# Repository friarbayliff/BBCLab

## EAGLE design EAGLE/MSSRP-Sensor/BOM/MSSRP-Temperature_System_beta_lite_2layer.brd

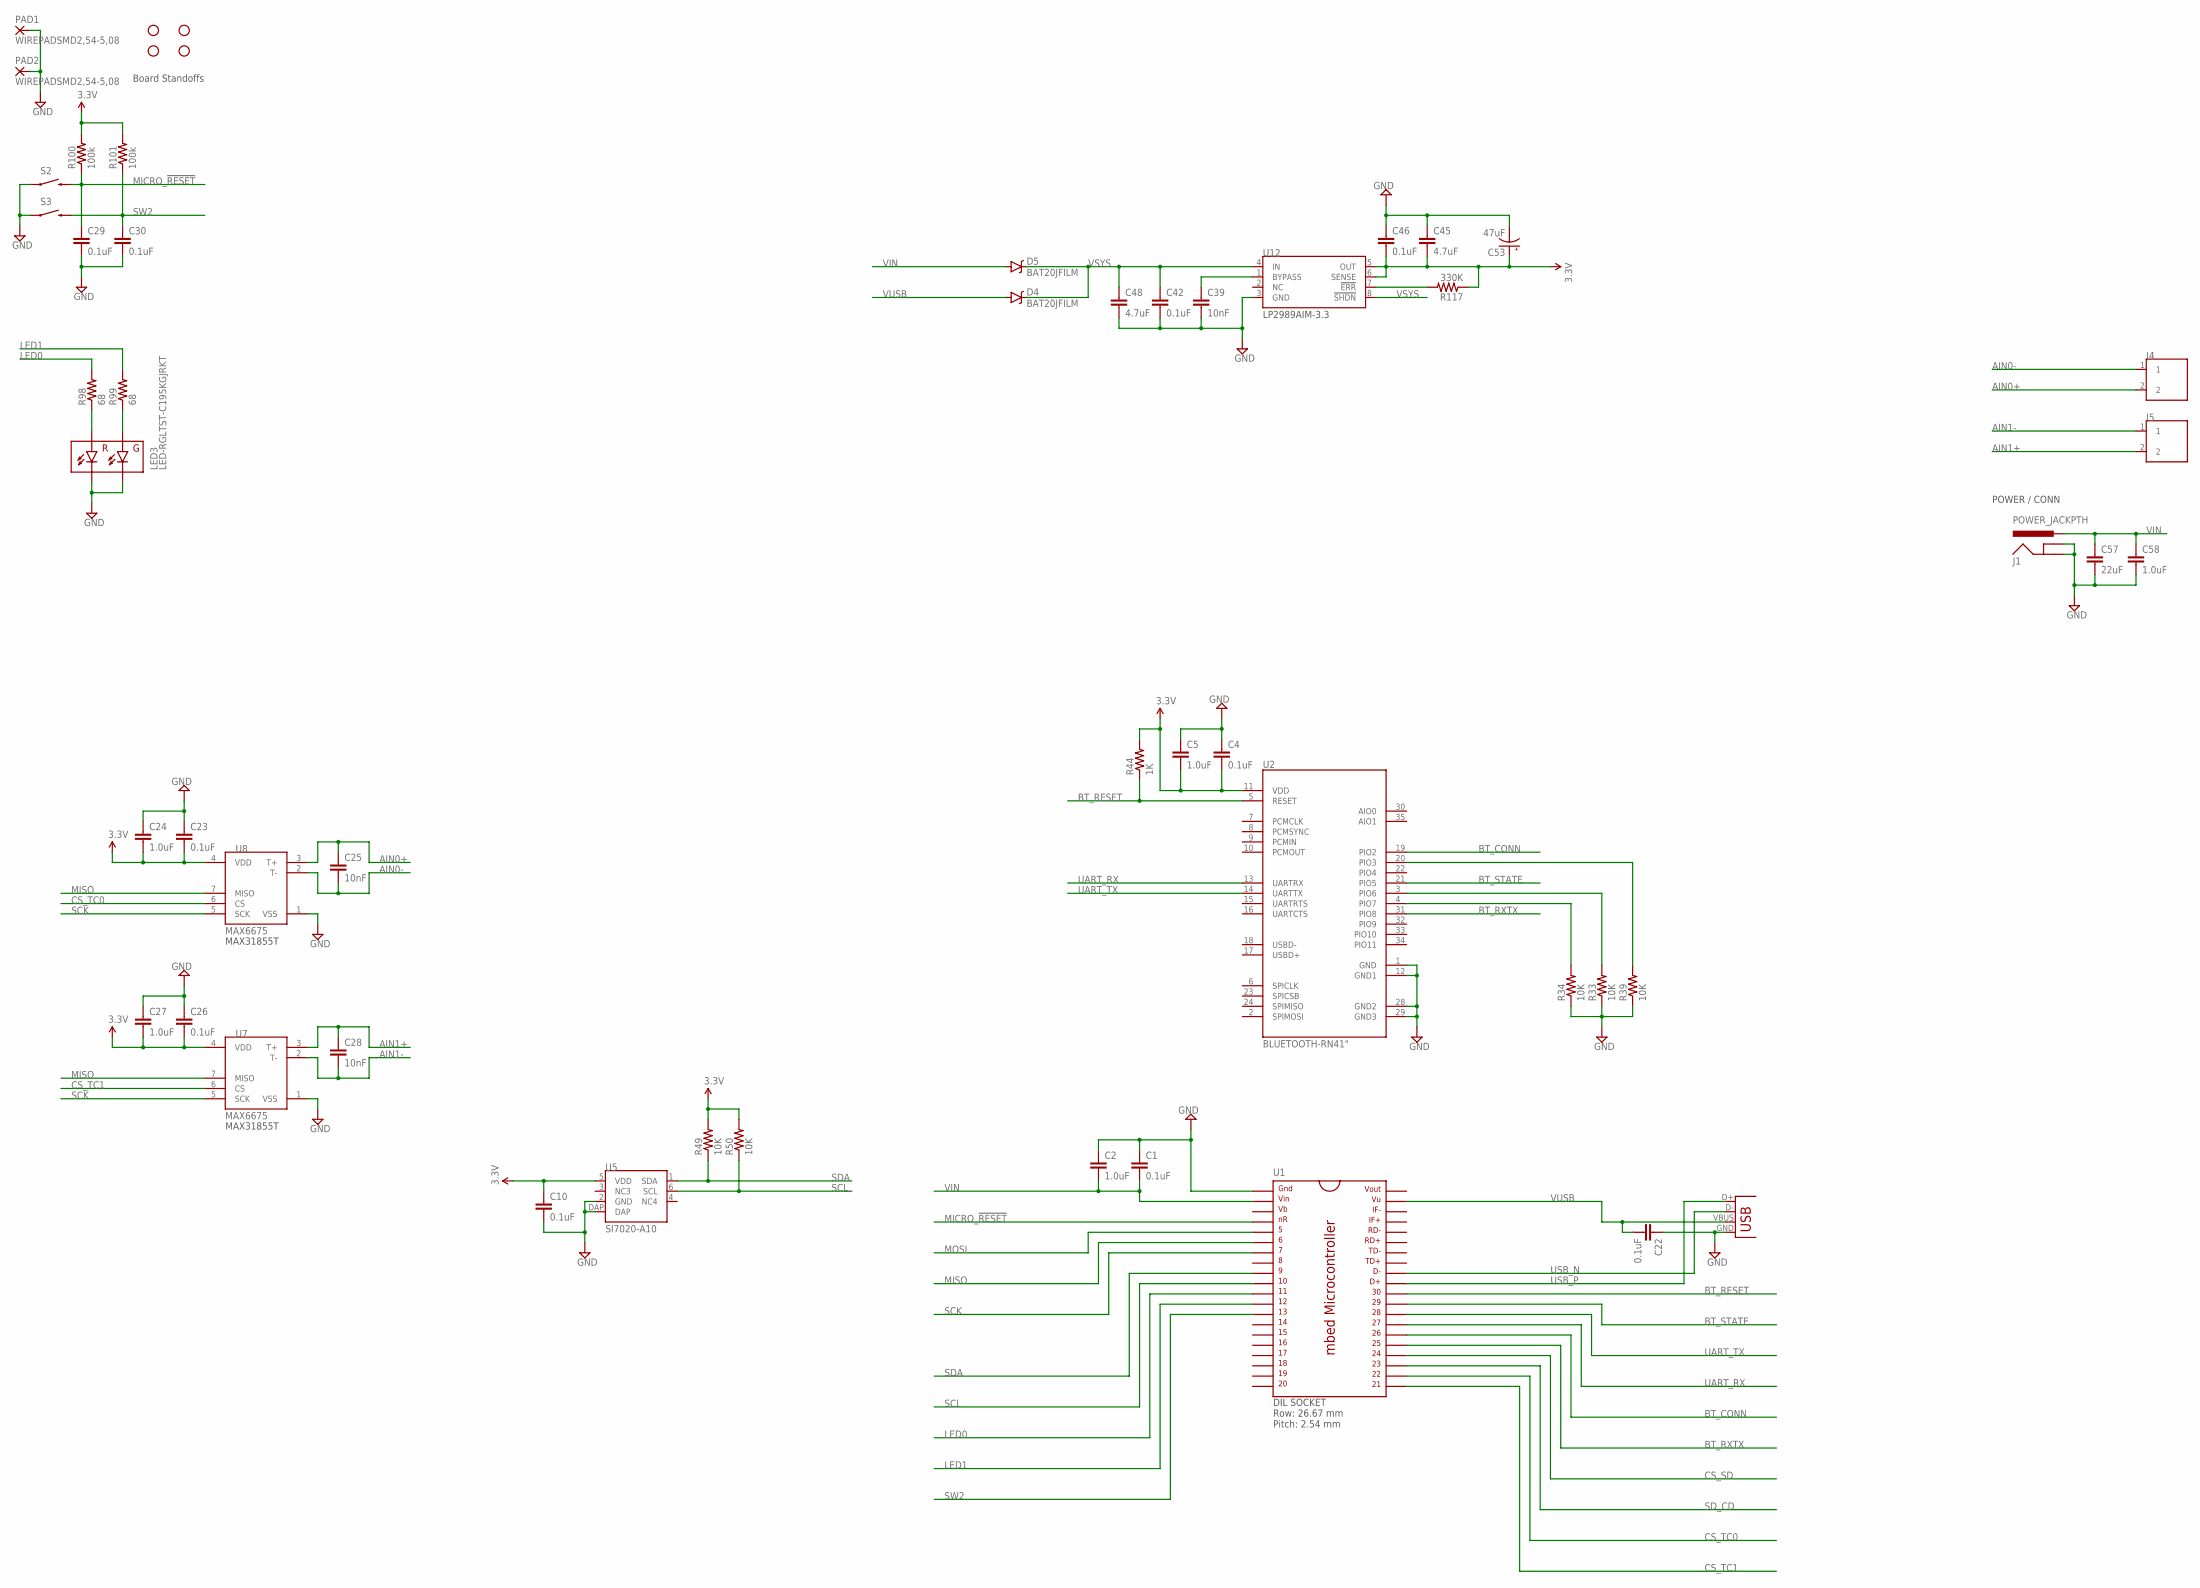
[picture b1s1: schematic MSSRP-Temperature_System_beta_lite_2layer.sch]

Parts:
C1, C4, C10, C22, C23, C26, C29, C30, C42, C46: 0.1uF; 0603-CAP
C2, C5, C24, C27, C58: 1.0uF; 0603-CAP
C25, C28, C39: 10nF; 0603-CAP
C45, C48: 4.7uF; 0603-CAP
C53: 47uF; EIA3528
C57: 22uF; 1210
D4, D5: BAT20JFILM; SOD-323
J1: POWER_JACKPTH; POWER_JACK_PTH
J4, J5: TE-2-TERMBLOCK
JP1: USB-A-SMD; USB-A-S-NOSILK-FEMALE
LED3: LED-RGLTST-C195KGJRKT; LTST-C195KGJRKT
PAD1, PAD2: WIREPADSMD2,54-5,08; SMD2,54-5,08
R33, R34, R39, R49, R50: 10K; 0603-RES
R44: 1K; 0603-RES
R98, R99: 68; 0603-RES
R100, R101: 100k; 0603-RES
R117: 330K; 0603-RES
S2, S3: SWITCH-MOMENTARY-2-SMD-1101NE; TACTILE-SWITCH-1101NE
STANDOFF1, STANDOFF2, STANDOFF3, STANDOFF4: STAND-OFF
U1: MBED; DIL40_0.9
U2: BLUETOOTH-RN41"; RN41
U5: SI7020-A10; DFN6
U7, U8: MAX6675; SO08-MAX6675
U12: LP2989AIM; SOIC8

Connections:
3.3V: C4.2, C5.2, C10.1, C23.2, C24.2, C26.2, C27.2, C45.2, C46.2, C53.A (+), R44.2, R49.2, R50.2, R100.2, R101.2, R117.1, U2.11 (VDD), U5.5 (VDD), U7.4 (VDD), U8.4 (VDD), U12.5 (OUT), U12.6 (SENSE)
AIN0+: C25.1, J4.2, U8.3 (T+)
AIN0-: C25.2, J4.1, U8.2 (T-)
AIN1+: C28.1, J5.2, U7.3 (T+)
AIN1-: C28.2, J5.1, U7.2 (T-)
BT_CONN: U1.26, U2.19 (PIO2)
BT_RESET: R44.1, U1.30, U2.5 (RESET)
BT_RXTX: U1.25, U2.31 (PIO8)
BT_STATE: U1.29, U2.21 (PIO5)
CS_SD: U1.24
CS_TC0: U1.22, U8.6 (CS)
CS_TC1: U1.21, U7.6 (CS)
GND: C1.1, C2.1, C4.1, C5.1, C10.2, C22.1, C23.1, C24.1, C26.1, C27.1, C29.2, C30.2, C39.2, C42.2, C45.1, C46.1, C48.2, C53.C (-), C57.2, C58.2, J1.GND, J1.GNDBREAK, JP1.GND, LED3.P$3 (GC), LED3.P$4 (RC), PAD1.1, PAD2.1, R33.1, R34.1, R39.1, S2.P$1 (1), S3.P$1 (1), U1.1, U2.1 (GND), U2.12 (GND1), U2.28 (GND2), U2.29 (GND3), U5.2 (GND), U5.DAP, U7.1 (VSS), U8.1 (VSS), U12.3 (GND)
LED0: R98.2, U1.11
LED1: R99.2, U1.12
MICRO_!RESET: C29.1, R100.1, S2.P$2 (2), U1.4
MISO: U1.6, U7.7 (MISO), U8.7 (MISO)
MOSI: U1.5
unnamed: R34.2, U2.4 (PIO7)
unnamed: R33.2, U2.3 (PIO6)
unnamed: R39.2, U2.20 (PIO3)
unnamed: LED3.P$2 (RA), R98.1
unnamed: LED3.P$1 (GA), R99.1
unnamed: C39.1, U12.1 (BYPASS)
unnamed: R117.2, U12.7 (!ERR)
SCK: U1.7, U7.5 (SCK), U8.5 (SCK)
SCL: R50.1, U1.10, U5.6 (SCL)
SDA: R49.1, U1.9, U5.1 (SDA)
SD_CD: U1.23
SW2: C30.1, R101.1, S3.P$2 (2), U1.13
UART_RX: U1.27, U2.13 (UARTRX)
UART_TX: U1.28, U2.14 (UARTTX)
USB_N: JP1.D-, U1.32
USB_P: JP1.D+, U1.31
VIN: C1.2, C2.2, C57.1, C58.1, D5.A, J1.PWR, U1.2
VSYS: C42.1, C48.1, D4.C, D5.C, U12.4 (IN), U12.8 (!SHDN)
VUSB: C22.2, D4.A, JP1.VBUS, U1.39

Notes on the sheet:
Board Standoffs
POWER / CONN
LP2989AIM-3.3
DIL SOCKET Row: 26.67 mm Pitch: 2.54 mm
MAX31855T

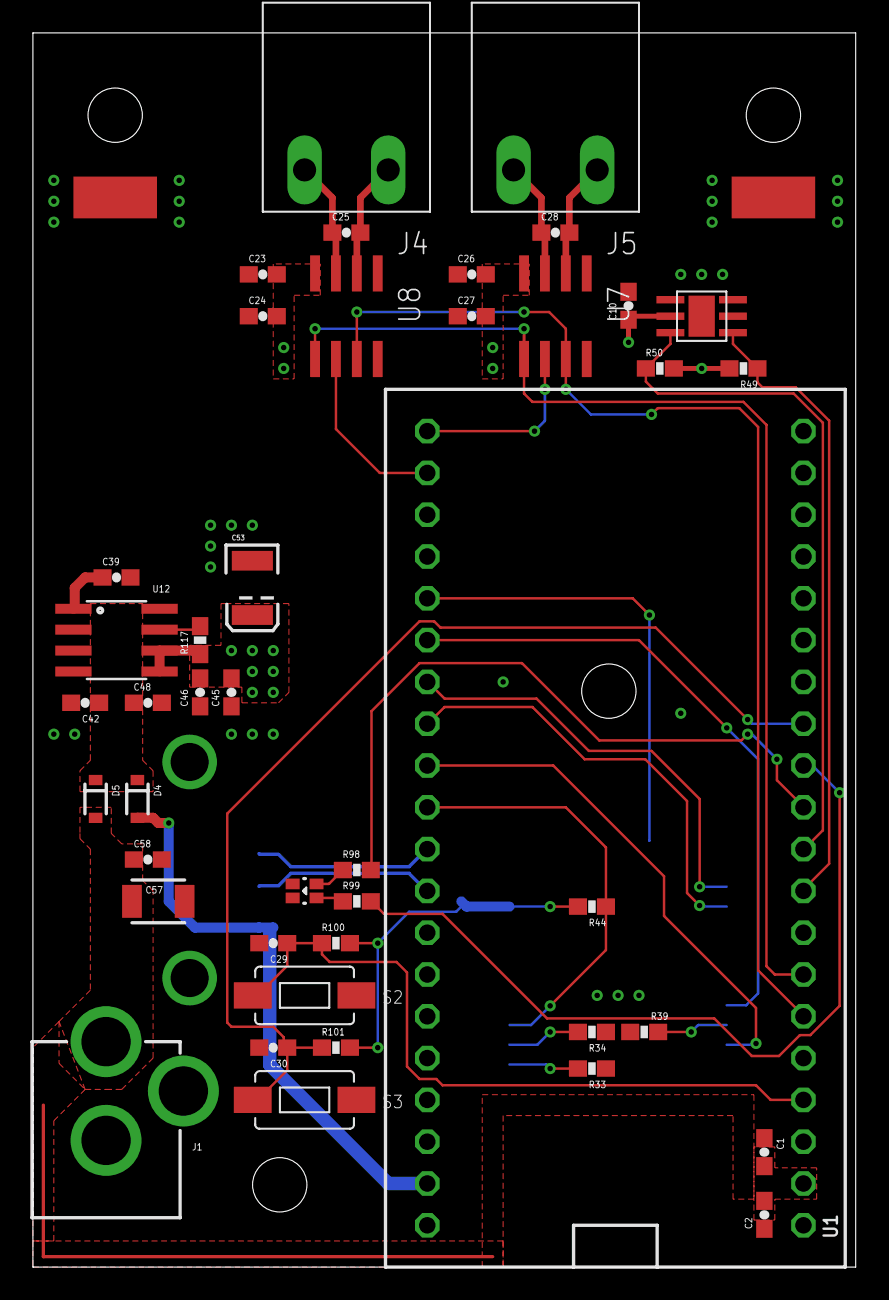
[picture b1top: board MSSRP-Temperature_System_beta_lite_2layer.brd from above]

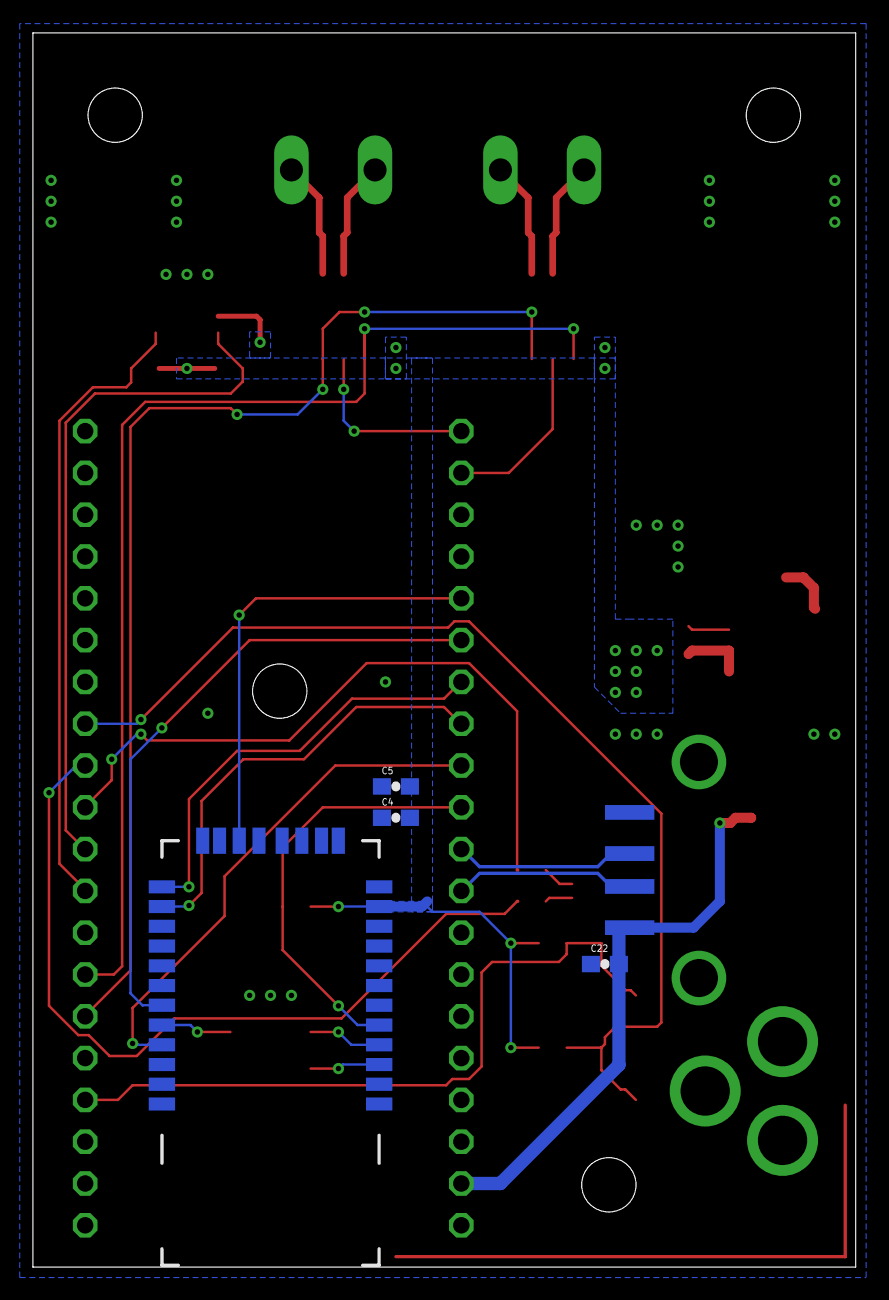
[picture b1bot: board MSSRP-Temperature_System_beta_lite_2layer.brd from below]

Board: 2 copper layers, 50.0 x 75.0 mm, 54 parts (5 on the bottom side), 34 nets.

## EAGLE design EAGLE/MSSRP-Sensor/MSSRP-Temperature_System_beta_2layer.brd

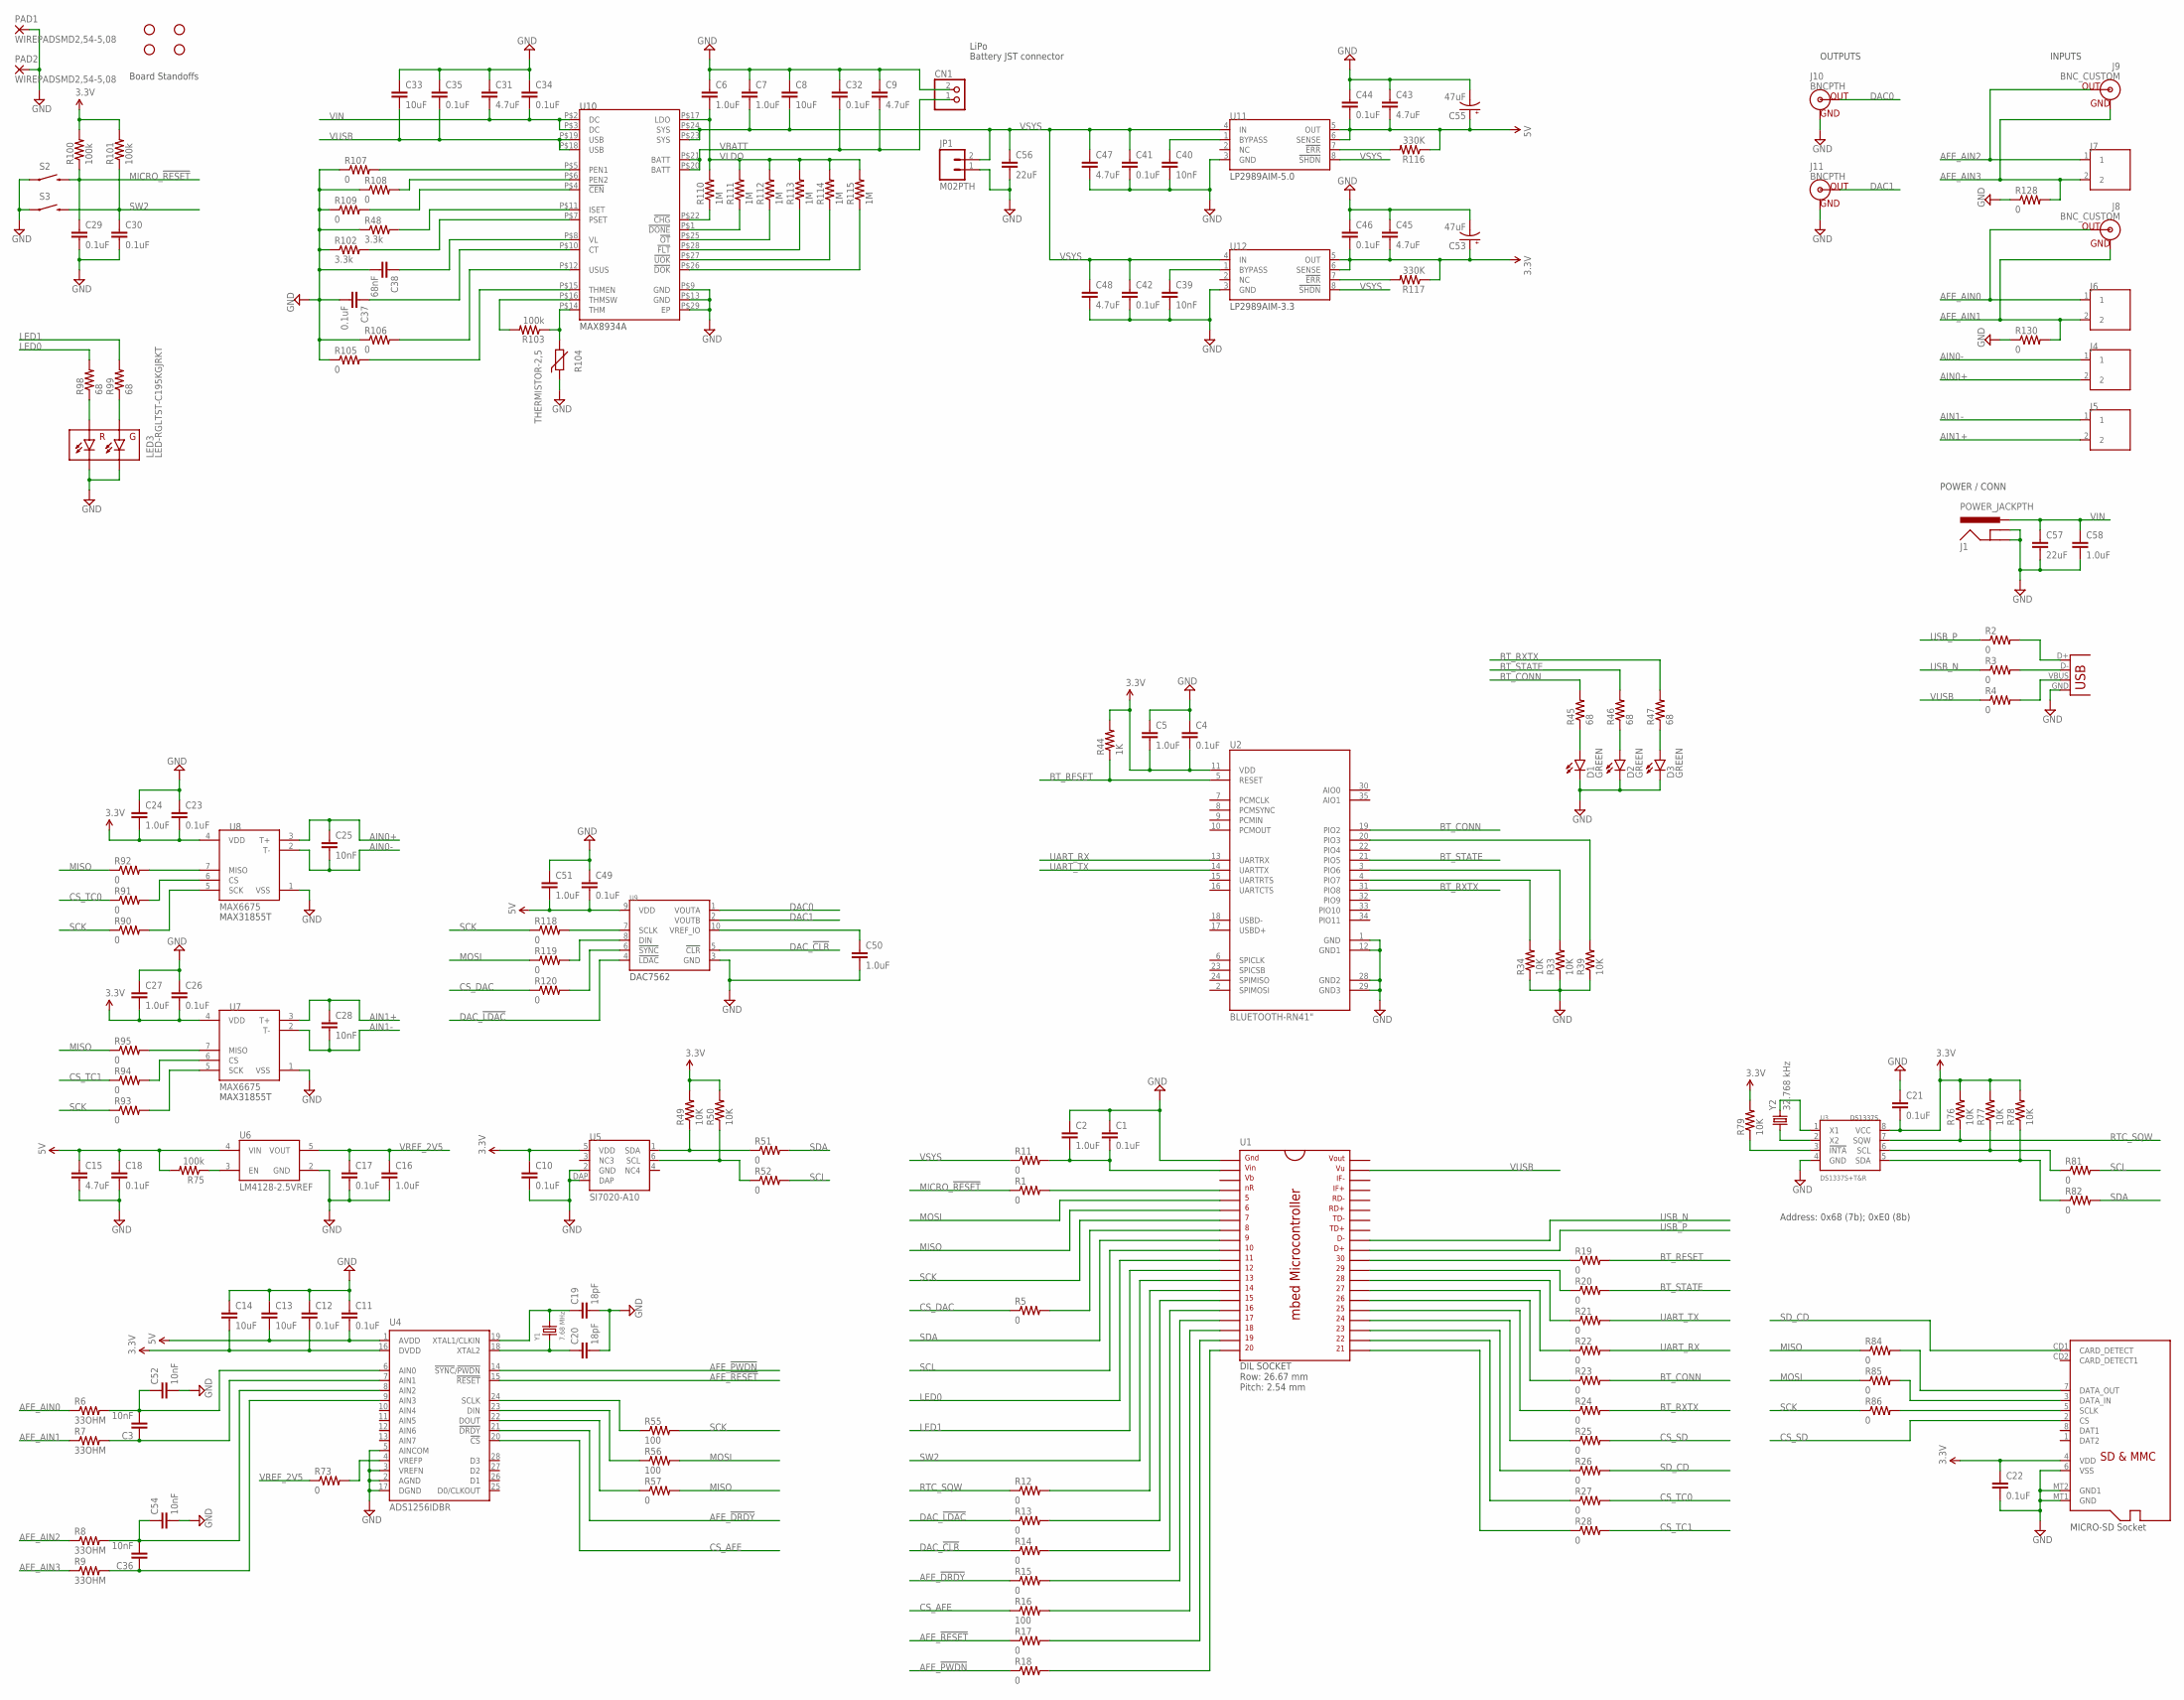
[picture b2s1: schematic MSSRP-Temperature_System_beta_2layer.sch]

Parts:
C1, C4, C10, C11, C12, C17, C18, C21, C22, C23, C26, C29, C30, C32, C34, C35, C37, C41, C42, C44, C46, C49: 0.1uF; 0603-CAP
C2, C5, C6, C7, C16, C24, C27, C50, C51, C58: 1.0uF; 0603-CAP
C3, C25, C28, C36, C39, C40, C52, C54: 10nF; 0603-CAP
C8, C13, C14, C33: 10uF; 0603-CAP
C9, C15, C31, C43, C45, C47, C48: 4.7uF; 0603-CAP
C19, C20: 18pF; 0603-CAP
C38: 68nF; 0603-CAP
C53, C55: 47uF; EIA3528
C56: 22uF; 0805
C57: 22uF; 1210
CN1: JST_2PIN-THM-RA; JST-PH-2-THM-RA
D1, D2, D3: GREEN; LED-0603
J1: POWER_JACKPTH; POWER_JACK_PTH
J2: USBSMD; USB-MINIB
J4, J5, J6, J7: TE-2-TERMBLOCK
J8, J9: BNC_CUSTOM
J10, J11: BNCPTH; BNC
JP1: M02PTH; 1X02
LED3: LED-RGLTST-C195KGJRKT; LTST-C195KGJRKT
PAD1, PAD2: WIREPADSMD2,54-5,08; SMD2,54-5,08
R1, R2, R3, R4, R5, R11, R12, R13, R14, R15, R17, R18, R19, R20, R21, R22, R23, R24, R25, R26, R27, R28, R51, R52, R57, R73, R81, R82, R84, R85, R86, R90, R91, R92, R93, R94, R95, R105, R106, R107, R108, R109, R118, R119, R120, R128, R130: 0; 0603
R6, R7, R8, R9: 33OHM; 0603
R16, R55, R56: 100; 0603-RES
R33, R34, R39, R49, R50, R76, R77, R78, R79: 10K; 0603-RES
R44: 1K; 0603-RES
R45, R46, R47, R98, R99: 68; 0603-RES
R48, R102: 3.3k; 0603-RES
R75, R100, R101, R103: 100k; 0603-RES
R104: THERMISTOR-2,5; RS-2,5
R110, R111, R112, R113, R114, R115: 1M; 0603-RES
R116, R117: 330K; 0603-RES
S2, S3: SWITCH-MOMENTARY-2-SMD-1101NE; TACTILE-SWITCH-1101NE
STANDOFF1, STANDOFF2, STANDOFF3, STANDOFF4: STAND-OFF
U1: MBED; DIL40_0.9
U2: BLUETOOTH-RN41"; RN41
U3: DS1337S+T&R; SOIC8
U4: ADS1256IDBR; SSOP28
U5: SI7020-A10; DFN6
U6: LM4128-2.5VREF; SOT23-5
U7, U8: MAX6675; SO08-MAX6675
U9: DAC7562; MSOP10
U10: MAX8934A; QFN28
U11, U12: LP2989AIM; SOIC8
U$1: MICROSD
Y1: 7.68 MHz; HC49UP
Y2: 32.768 kHz; HC49UP

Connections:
3.3V: C4.2, C5.2, C10.1, C12.2, C14.2, C21.2, C22.1, C23.2, C24.2, C26.2, C27.2, C45.2, C46.2, C53.A (+), R44.2, R49.2, R50.2, R76.2, R77.2, R78.2, R79.2, R100.2, R101.2, R117.1, U2.11 (VDD), U3.8 (VCC), U4.16 (DVDD), U5.5 (VDD), U7.4 (VDD), U8.4 (VDD), U12.5 (OUT), U12.6 (SENSE), U$1.4 (VDD)
5V: C11.2, C13.2, C15.1, C18.1, C43.2, C44.2, C49.2, C51.2, C55.A (+), R75.2, R116.1, U4.1 (AVDD), U6.4 (VIN), U9.9 (VDD), U11.5 (OUT), U11.6 (SENSE)
AFE_!DRDY: R15.1, U4.21 (!DRDY)
AFE_!PWDN: R18.1, U4.14 (!SYNC!/!PWDN)
AFE_!RESET: R17.1, U4.15 (!RESET)
AFE_AIN0: J6.1, J8.S (OUT), R6.1
AFE_AIN1: J6.2, J8.GND, R7.1, R130.2
AFE_AIN2: J7.1, J9.S (OUT), R8.1
AFE_AIN3: J7.2, J9.GND, R9.1, R128.2
AIN0+: C25.1, J4.2, U8.3 (T+)
AIN0-: C25.2, J4.1, U8.2 (T-)
AIN1+: C28.1, J5.2, U7.3 (T+)
AIN1-: C28.2, J5.1, U7.2 (T-)
BT_CONN: R23.2, R45.2, U2.19 (PIO2)
BT_RESET: R19.2, R44.1, U2.5 (RESET)
BT_RXTX: R24.2, R47.2, U2.31 (PIO8)
BT_STATE: R20.2, R46.2, U2.21 (PIO5)
CS_AFE: R16.1, U4.20 (!CS)
CS_DAC: R5.1, R120.1
CS_SD: R25.2, U$1.2 (CS)
CS_TC0: R27.2, R91.1
CS_TC1: R28.2, R94.1
DAC0: J10.S (OUT), U9.1 (VOUTA)
DAC1: J11.S (OUT), U9.2 (VOUTB)
DAC_!CLR: R14.1, U9.5 (!CLR)
DAC_!LDAC: R13.1, U9.4 (!LDAC)
GND: C1.1, C2.1, C4.1, C5.1, C6.1, C7.1, C8.1, C9.1, C10.2, C11.1, C12.1, C13.1, C14.1, C15.2, C16.2, C17.2, C18.2, C19.2, C20.2, C21.1, C22.2, C23.1, C24.1, C26.1, C27.1, C29.2, C30.2, C31.1, C32.1, C33.1, C34.1, C35.1, C37.2, C38.2, C39.2, C40.2, C41.2, C42.2, C43.1, C44.1, C45.1, C46.1, C47.2, C48.2, C49.1, C50.2, C51.1, C52.2, C53.C (-), C54.2, C55.C (-), C56.2, C57.2, C58.2, CN1.2 (1), D1.C, D2.C, D3.C, J1.GND, J1.GNDBREAK, J2.GND, J10.GND, J11.GND, JP1.1, LED3.P$3 (GC), LED3.P$4 (RC), PAD1.1, PAD2.1, R33.1, R34.1, R39.1, R48.1, R102.1, R104.1, R105.1, R106.1, R107.1, R108.1, R109.1, R128.1, R130.1, S2.P$1 (1), S3.P$1 (1), U1.1, U2.1 (GND), U2.12 (GND1), U2.28 (GND2), U2.29 (GND3), U3.4 (GND), U4.2 (AGND), U4.3 (VREFN), U4.5 (AINCOM), U4.17 (DGND), U5.2 (GND), U5.DAP, U6.2 (GND), U7.1 (VSS), U8.1 (VSS), U9.3 (GND), U10.P$9 (GND), U10.P$13 (GND), U10.P$29 (EP), U11.3 (GND), U12.3 (GND), U$1.6 (VSS), U$1.MT1 (GND), U$1.MT2 (GND1)
LED0: R98.2, U1.11
LED1: R99.2, U1.12
MICRO_!RESET: C29.1, R1.1, R100.1, S2.P$2 (2)
MISO: R57.2, R84.1, R92.1, R95.1, U1.6
MOSI: R56.2, R85.1, R119.1, U1.5
unnamed: R1.2, U1.4
unnamed: J2.D-, R3.2
unnamed: J2.D+, R2.2
unnamed: J2.VBUS, R4.2
unnamed: R5.2, U1.8
unnamed: C3.1, R7.2, U4.7 (AIN1)
unnamed: C1.2, C2.2, R11.2, U1.2
unnamed: C3.2, C52.1, R6.2, U4.6 (AIN0)
unnamed: C36.2, C54.1, R8.2, U4.8 (AIN2)
unnamed: C36.1, R9.2, U4.9 (AIN3)
unnamed: R12.2, U1.14
unnamed: R19.1, U1.30
unnamed: R13.2, U1.15
unnamed: R20.1, U1.29
unnamed: R21.1, U1.28
unnamed: R22.1, U1.27
unnamed: R23.1, U1.26
unnamed: R24.1, U1.25
unnamed: R14.2, U1.16
unnamed: R15.2, U1.17
unnamed: R16.2, U1.18
unnamed: R17.2, U1.19
unnamed: R18.2, U1.20
unnamed: R25.1, U1.24
unnamed: R26.1, U1.23
unnamed: R27.1, U1.22
unnamed: R28.1, U1.21
unnamed: R34.2, U2.4 (PIO7)
unnamed: R33.2, U2.3 (PIO6)
unnamed: R39.2, U2.20 (PIO3)
unnamed: D1.A, R45.1
unnamed: D2.A, R46.1
unnamed: D3.A, R47.1
unnamed: R49.1, R51.1, U5.1 (SDA)
unnamed: R50.1, R52.1, U5.6 (SCL)
unnamed: R55.1, U4.24 (SCLK)
unnamed: R56.1, U4.23 (DIN)
unnamed: R57.1, U4.22 (DOUT)
unnamed: R73.2, U4.4 (VREFP)
unnamed: R75.1, U6.3 (EN)
unnamed: C20.1, U4.18 (XTAL2), Y1.1
unnamed: C19.1, U4.19 (XTAL1/CLKIN), Y1.2
unnamed: U3.2 (X2), Y2.1
unnamed: U3.1 (X1), Y2.2
unnamed: R77.1, R81.1, U3.6 (SCL)
unnamed: R78.1, R82.1, U3.5 (SDA)
unnamed: R86.2, U$1.5 (SCLK)
unnamed: R85.2, U$1.3 (DATA_IN)
unnamed: R84.2, U$1.7 (DATA_OUT)
unnamed: R92.2, U8.7 (MISO)
unnamed: R91.2, U8.6 (CS)
unnamed: R90.2, U8.5 (SCK)
unnamed: R95.2, U7.7 (MISO)
unnamed: R94.2, U7.6 (CS)
unnamed: R93.2, U7.5 (SCK)
unnamed: LED3.P$2 (RA), R98.1
unnamed: LED3.P$1 (GA), R99.1
unnamed: R103.1, R104.2, U10.P$14 (THM)
unnamed: R103.2, U10.P$16 (THMSW)
unnamed: R105.2, U10.P$15 (THMEN)
unnamed: R106.2, U10.P$12 (USUS)
unnamed: R107.2, U10.P$5 (PEN1)
unnamed: R108.2, U10.P$6 (PEN2)
unnamed: R109.2, U10.P$4 (!CEN)
unnamed: R48.2, U10.P$11 (ISET)
unnamed: R102.2, U10.P$7 (PSET)
unnamed: C38.1, U10.P$8 (VL)
unnamed: C37.1, U10.P$10 (CT)
unnamed: R110.1, U10.P$22 (!CHG)
unnamed: R111.1, U10.P$1 (!DONE)
unnamed: R112.1, U10.P$25 (!OT)
unnamed: R113.1, U10.P$28 (!FLT)
unnamed: R114.1, U10.P$27 (!UOK)
unnamed: R115.1, U10.P$26 (!DOK)
unnamed: C40.1, U11.1 (BYPASS)
unnamed: C39.1, U12.1 (BYPASS)
unnamed: R116.2, U11.7 (!ERR)
unnamed: R117.2, U12.7 (!ERR)
unnamed: R118.2, U9.7 (SCLK)
unnamed: R119.2, U9.8 (DIN)
unnamed: R120.2, U9.6 (!SYNC)
unnamed: C50.1, U9.10 (VREF_IO)
RTC_!INTA: R79.1, U3.3 (!INTA)
RTC_SQW: R12.1, R76.1, U3.7 (SQW)
SCK: R55.2, R86.1, R90.1, R93.1, R118.1, U1.7
SCL: R52.2, R81.2, U1.10
SDA: R51.2, R82.2, U1.9
SD_CD: R26.2, U$1.CD1 (CARD_DETECT)
SW2: C30.1, R101.1, S3.P$2 (2), U1.13
UART_RX: R22.2, U2.13 (UARTRX)
UART_TX: R21.2, U2.14 (UARTTX)
USB_N: R3.1, U1.32
USB_P: R2.1, U1.31
VBATT: C9.2, C32.2, CN1.1 (2), U10.P$20 (BATT), U10.P$21 (BATT)
VIN: C31.2, C34.2, C57.1, C58.1, J1.PWR, U10.P$2 (DC), U10.P$3 (DC)
VLDO: C6.2, R110.2, R111.2, R112.2, R113.2, R114.2, R115.2, U10.P$17 (LDO)
VREF_2V5: C16.1, C17.1, R73.1, U6.5 (VOUT)
VSYS: C7.2, C8.2, C41.1, C42.1, C47.1, C48.1, C56.1, JP1.2, R11.1, U10.P$23 (SYS), U10.P$24 (SYS), U11.4 (IN), U11.8 (!SHDN), U12.4 (IN), U12.8 (!SHDN)
VUSB: C33.2, C35.2, R4.1, U1.39, U10.P$18 (USB), U10.P$19 (USB)

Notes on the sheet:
Board Standoffs
Address: 0x68 (7b); 0xE0 (8b)
LiPo
Battery JST connector
OUTPUTS
INPUTS
POWER / CONN
DAC7562
LP2989AIM-5.0
LP2989AIM-3.3
MAX8934A
DIL SOCKET Row: 26.67 mm Pitch: 2.54 mm
MICRO-SD Socket
MAX31855T
U10

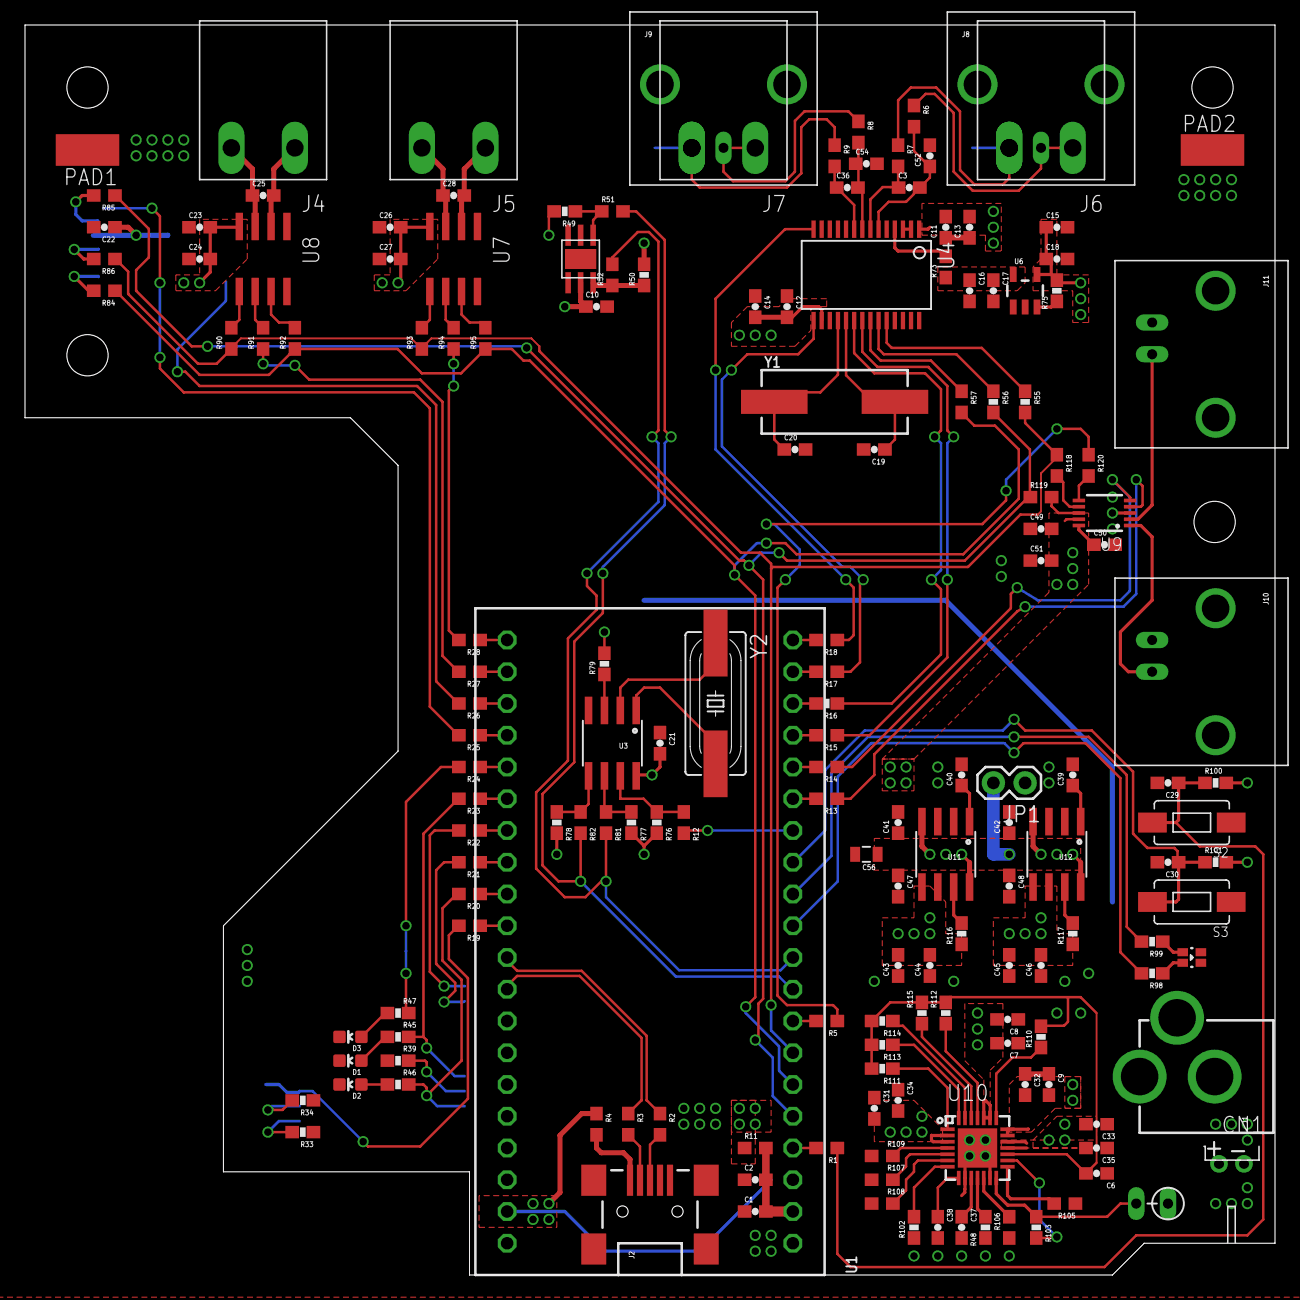
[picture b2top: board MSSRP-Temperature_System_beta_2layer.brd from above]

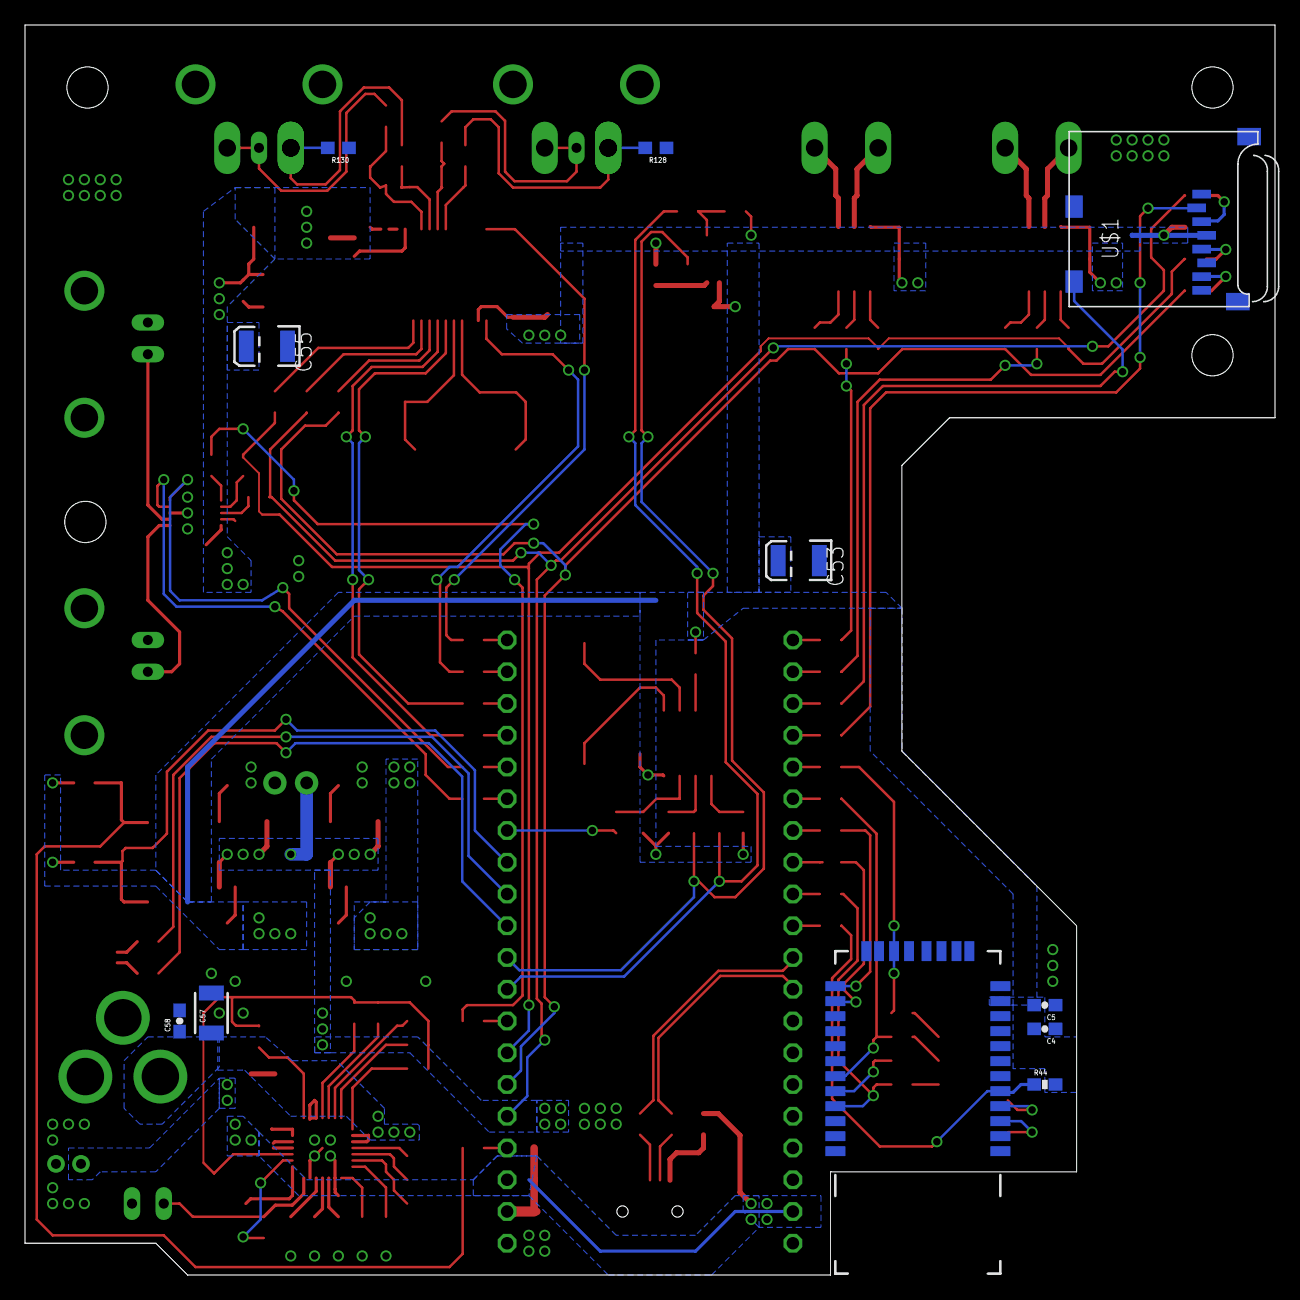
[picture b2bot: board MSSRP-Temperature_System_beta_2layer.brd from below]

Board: 2 copper layers, 100.0 x 100.0 mm, 181 parts (11 on the bottom side), 131 nets.

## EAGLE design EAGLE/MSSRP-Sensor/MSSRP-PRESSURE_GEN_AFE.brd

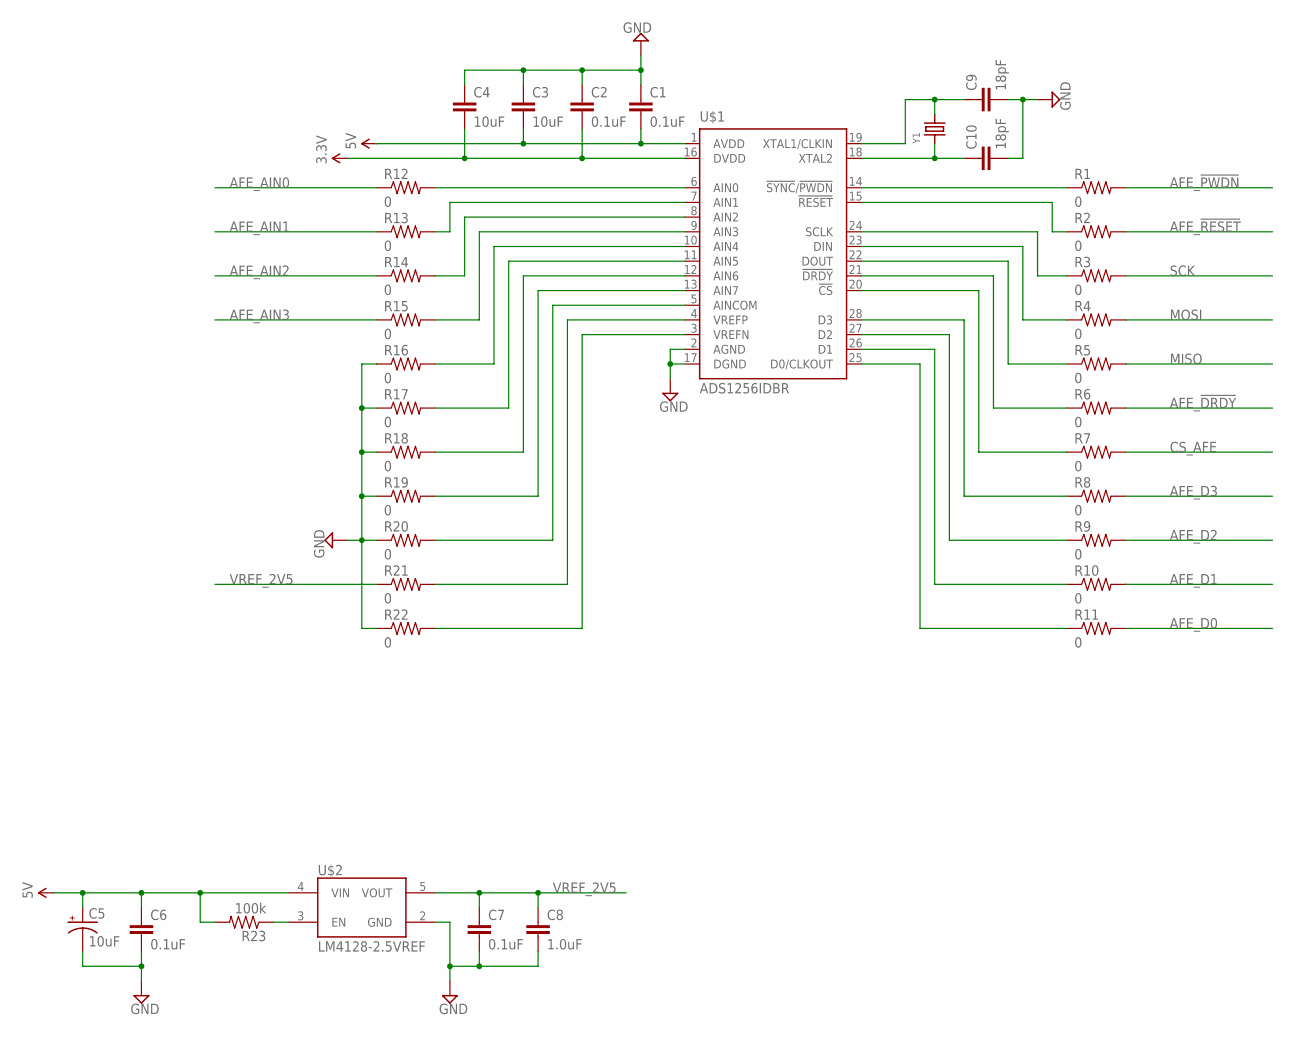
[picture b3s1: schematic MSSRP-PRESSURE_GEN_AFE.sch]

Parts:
C1, C2, C6, C7: 0.1uF; 0603-CAP
C3, C4: 10uF; 0603-CAP
C5: 10uF; EIA3216
C8: 1.0uF; 0603-CAP
C9, C10: 18pF; 0603-CAP
R1, R2, R3, R4, R5, R6, R7, R8, R9, R10, R11, R12, R13, R14, R15, R16, R17, R18, R19, R20, R21, R22: 0; 0603
R23: 100k; 0603-RES
U$1: ADS1256IDBR; SSOP28
U$2: LM4128-2.5VREF; SOT23-5
Y1: CRYSTALSMD; HC49UP

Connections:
3.3V: C2.2, C4.2, U$1.16 (DVDD)
5V: C1.2, C3.2, C5.A (+), C6.1, R23.2, U$1.1 (AVDD), U$2.4 (VIN)
AFE_!DRDY: R6.2
AFE_!PWDN: R1.2
AFE_!RESET: R2.2
AFE_AIN0: R12.1
AFE_AIN1: R13.1
AFE_AIN2: R14.1
AFE_AIN3: R15.1
AFE_D0: R11.2
AFE_D1: R10.2
AFE_D2: R9.2
AFE_D3: R8.2
CS_AFE: R7.2
GND: C1.1, C2.1, C3.1, C4.1, C5.C (-), C6.2, C7.2, C8.2, C9.2, C10.2, R16.1, R17.1, R18.1, R19.1, R20.1, R22.1, U$1.2 (AGND), U$1.17 (DGND), U$2.2 (GND)
MISO: R5.2
MOSI: R4.2
unnamed: R12.2, U$1.6 (AIN0)
unnamed: R13.2, U$1.7 (AIN1)
unnamed: R14.2, U$1.8 (AIN2)
unnamed: R15.2, U$1.9 (AIN3)
unnamed: R1.1, U$1.14 (!SYNC!/!PWDN)
unnamed: R2.1, U$1.15 (!RESET)
unnamed: R3.1, U$1.24 (SCLK)
unnamed: R4.1, U$1.23 (DIN)
unnamed: R5.1, U$1.22 (DOUT)
unnamed: R6.1, U$1.21 (!DRDY)
unnamed: R7.1, U$1.20 (!CS)
unnamed: R8.1, U$1.28 (D3)
unnamed: R9.1, U$1.27 (D2)
unnamed: R10.1, U$1.26 (D1)
unnamed: R11.1, U$1.25 (D0/CLKOUT)
unnamed: R16.2, U$1.10 (AIN4)
unnamed: R17.2, U$1.11 (AIN5)
unnamed: R18.2, U$1.12 (AIN6)
unnamed: R19.2, U$1.13 (AIN7)
unnamed: R20.2, U$1.5 (AINCOM)
unnamed: R21.2, U$1.4 (VREFP)
unnamed: R22.2, U$1.3 (VREFN)
unnamed: R23.1, U$2.3 (EN)
unnamed: C10.1, U$1.18 (XTAL2), Y1.1
unnamed: C9.1, U$1.19 (XTAL1/CLKIN), Y1.2
SCK: R3.2
VREF_2V5: C7.1, C8.1, R21.1, U$2.5 (VOUT)

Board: 2 copper layers, 36 parts (0 on the bottom side), 29 nets, no tracks yet.

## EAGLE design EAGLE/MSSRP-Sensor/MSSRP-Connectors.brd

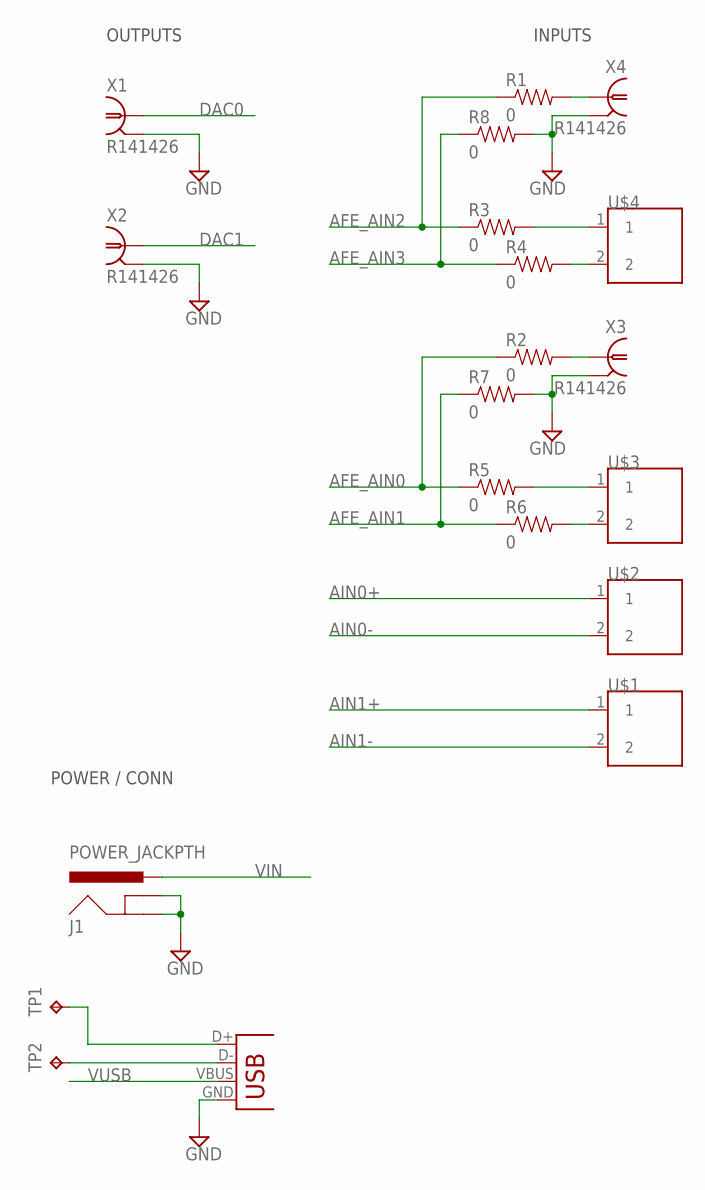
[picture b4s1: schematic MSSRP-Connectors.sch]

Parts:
J1: POWER_JACKPTH; POWER_JACK_PTH
JP1: USBSMD; USB-MINIB
R1, R2, R3, R4, R5, R6, R7, R8: 0; 0603
TP1, TP2: TPPAD1-13; P1-13
U$1, U$2, U$3, U$4: TE-2-TERMBLOCK
X1, X2, X3, X4: R141426

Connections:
AFE_AIN0: R2.1, R5.1
AFE_AIN1: R6.1, R7.1
AFE_AIN2: R1.1, R3.1
AFE_AIN3: R4.1, R8.1
AIN0+: U$2.1
AIN0-: U$2.2
AIN1+: U$1.1
AIN1-: U$1.2
DAC0: X1.1
DAC1: X2.1
GND: J1.GND, J1.GNDBREAK, JP1.GND, R7.2, R8.2, X1.2, X1.3 (2), X1.4 (2), X1.5 (2), X2.2, X2.3 (2), X2.4 (2), X2.5 (2), X3.2, X3.3 (2), X3.4 (2), X3.5 (2), X4.2, X4.3 (2), X4.4 (2), X4.5 (2)
unnamed: JP1.D-, TP2.TP
unnamed: R2.2, X3.1
unnamed: JP1.D+, TP1.TP
unnamed: R1.2, X4.1
unnamed: R3.2, U$4.1
unnamed: R4.2, U$4.2
unnamed: R5.2, U$3.1
unnamed: R6.2, U$3.2
VIN: J1.PWR
VUSB: JP1.VBUS

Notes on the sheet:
OUTPUTS
INPUTS
POWER / CONN

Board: 2 copper layers, 20 parts (0 on the bottom side), 13 nets, no tracks yet.

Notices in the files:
parts and their libraries:
microbuilder: This work is placed in the public domain, and may be freely used for commercial and non-commercial work with the following conditions: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
SparkFun-Capacitors: Licensing: Creative Commons ShareAlike 4.0 International - https://creativecommons.org/licenses/by-sa/4.0
